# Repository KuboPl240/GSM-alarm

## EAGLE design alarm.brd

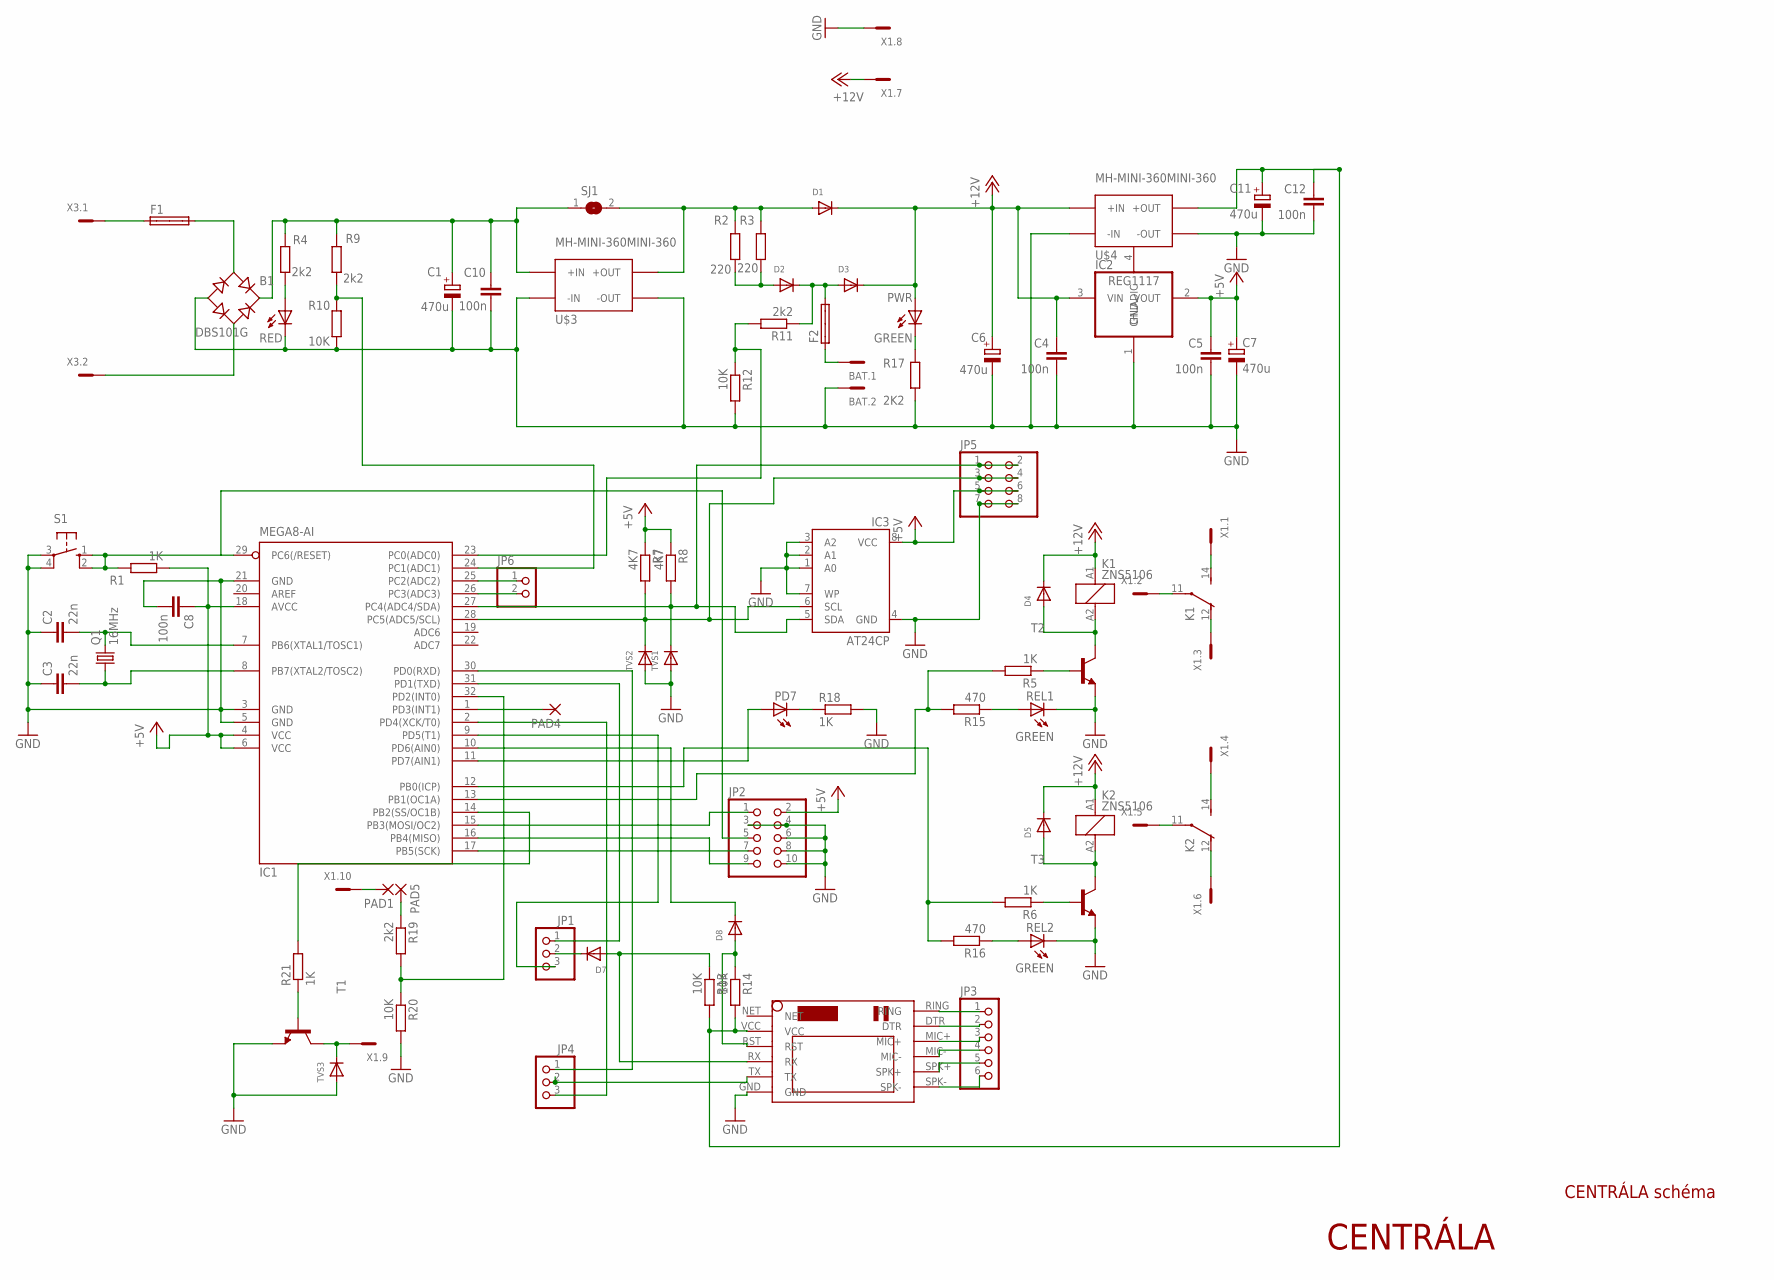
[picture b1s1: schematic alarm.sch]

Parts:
B1: DBS101G; DBS
BAT: MCV2
C1, C6, C7, C11: 470u; 153CLV-0810
C2, C3: 22n; C0805
C4, C5, C8, C10, C12: 100n; C0805
D1, D2, D3, D4, D5, D7, D8: DIODE_SOD-123FL; SOD-123FL
F1, F2: SHK20L
IC1: MEGA8-AI; TQFP32-08
IC2: REG1117; SOT223
IC3: AT24CP; DIL08
JP1, JP4: PINHD-1X3; 1X03
JP2: PINHD-2X5; 2X05
JP3: PINHD-1X6; 1X06
JP5: PINHD-2X4; 2X04
JP6: PINHD-1X2; 1X02
K1, K2: ZNS5106; ZN5
PAD1, PAD4, PAD5: 2,54/0,8
PD7: LEDCHIPLED_0805; CHIPLED_0805
PWR: GREEN; CHIPLED_0805
Q1: 16MHz; HC49UP
R1, R5, R6, R18, R21: 1K; R0805
R2, R3: 220; R1210
R4, R9, R11, R19: 2k2; R0805
R7, R8: 4K7; R0805
R10, R12, R13, R14, R20: 10K; R0805
R15, R16: 470; R0805
R17: 2K2; R0805
REL1, REL2: GREEN; CHIPLED_0805
S1: 10-XX; B3F-10XX
SJ1: SJW
SUPPLY: RED; CHIPLED_0805
T1, T2, T3: BC808-NPN-SOT23-BEC; SOT23-BEC
TVS1, TVS2, TVS3: DIODE_SOD-123FL; SOD-123FL
U$1: SIM800LMODULE
U$3, U$4: MH-MINI-360MINI-360; MH-MINI-360
X1: MCV10
X3: MCV2

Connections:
+4.4V: C11.+, C12.2, R13.2, R14.2, U$1.VCC, U$4.P$3 (+OUT)
+5V: C5.2, C7.+, C8.1, IC1.4 (VCC), IC1.6 (VCC), IC1.18 (AVCC), IC2.2 (VOUT), IC3.8 (VCC), JP2.2, JP5.5, JP5.6, R1.1, R7.1, R8.1
+12V: C4.2, C6.+, D1.C, D3.C, D4.C, D5.C, IC2.3 (VIN), K1.A1 (1), K2.A1 (1), PWR.A, U$4.P$2 (+IN), X1.7
CHLADIC: IC2.4 (CHLADIC)
GND: B1.-, BAT.2, C1.-, C2.1, C3.1, C4.1, C5.1, C6.-, C7.-, C8.2, C10.1, C11.-, C12.1, IC1.3 (GND), IC1.5 (GND), IC1.21 (GND), IC2.1 (GND), IC3.1 (A0), IC3.2 (A1), IC3.3 (A2), IC3.4 (GND), IC3.7 (WP), JP2.3, JP2.4, JP2.6, JP2.8, JP2.10, JP5.7, JP5.8, R10.2, R12.2, R17.2, R18.2, R20.2, REL1.C, REL2.C, S1.3, S1.4 (P1), SUPPLY.C, T1.E, T2.E, T3.E, TVS1.A, TVS2.A, TVS3.A, U$1.GND, U$3.P$1 (-IN), U$3.P$4 (-OUT), U$4.P$1 (-IN), U$4.P$4 (-OUT), X1.8
unnamed: B1.AC1, F1.2A
unnamed: B1.AC2, X3.2
unnamed: B1.+, C1.+, C10.2, R4.1, R9.1, SJ1.1, U$3.P$2 (+IN)
unnamed: JP3.6, U$1.SPK-
unnamed: D1.A, R2.2, R3.2, SJ1.2, U$3.P$3 (+OUT)
unnamed: D2.A, R2.1, R3.1
unnamed: D2.C, D3.A, F2.2A, R11.1
unnamed: BAT.1, F2.1A
unnamed: C3.2, IC1.8 (PB7(XTAL2/TOSC2)), Q1.1
unnamed: F1.1A, X3.1
unnamed: IC1.15 (PB3(MOSI/OC2)), JP2.1
unnamed: C2.2, IC1.7 (PB6(XTAL1/TOSC1)), Q1.2
unnamed: IC1.17 (PB5(SCK)), JP2.7
unnamed: R4.2, SUPPLY.A
unnamed: IC1.29 (PC6(/RESET)), JP2.5, R1.2, S1.1 (S), S1.2 (S1)
unnamed: IC1.16 (PB4(MISO)), JP2.9
unnamed: IC1.28 (PC5(ADC5/SCL)), IC3.6 (SCL), JP5.3, JP5.4, R7.2, TVS2.C
unnamed: PAD1.1, X1.10
unnamed: IC1.24 (PC1(ADC1)), R9.2, R10.1
unnamed: D5.A, K2.A2 (2), T3.C
unnamed: D4.A, K1.A2 (2), T2.C
unnamed: R5.1, T2.B
unnamed: R6.1, T3.B
unnamed: IC1.13 (PB1(OC1A)), R5.2, R15.2
unnamed: K1.14 (S), X1.1
unnamed: K1.11, X1.2
unnamed: K1.12 (O), X1.3
unnamed: K2.14 (S), X1.4
unnamed: K2.11, X1.5
unnamed: K2.12 (O), X1.6
unnamed: IC1.23 (PC0(ADC0)), R11.2, R12.1
unnamed: JP3.5, U$1.SPK+
unnamed: JP3.4, U$1.MIC-
unnamed: JP3.3, U$1.MIC+
unnamed: JP3.2, U$1.DTR
unnamed: JP3.1, U$1.RING
unnamed: JP4.2, U$1.TX
unnamed: D7.A, R13.1, U$1.RX
unnamed: IC1.31 (PD1(TXD)), JP1.1
unnamed: IC1.30 (PD0(RXD)), JP4.1
unnamed: IC1.2 (PD4(XCK/T0)), JP4.3
unnamed: D7.C, JP1.2
unnamed: IC1.9 (PD5(T1)), JP1.3
unnamed: D8.A, R14.1, U$1.RST
unnamed: R16.1, REL2.A
unnamed: D8.C, IC1.10 (PD6(AIN0))
unnamed: R15.1, REL1.A
unnamed: PWR.C, R17.1
unnamed: PD7.C, R18.1
unnamed: IC1.11 (PD7(AIN1)), PD7.A
unnamed: IC1.27 (PC4(ADC4/SDA)), IC3.5 (SDA), JP5.1, JP5.2, R8.2, TVS1.C
unnamed: IC1.32 (PD2(INT0)), R19.2, R20.1
unnamed: IC1.14 (PB2(SS/OC1B)), R21.2
unnamed: IC1.25 (PC2(ADC2)), JP6.1
unnamed: IC1.26 (PC3(ADC3)), JP6.2
unnamed: IC1.1 (PD3(INT1)), PAD4.1
unnamed: R21.1, T1.B
unnamed: T1.C, TVS3.C, X1.9
unnamed: PAD5.1, R19.1
unnamed: IC1.12 (PB0(ICP)), R6.2, R16.2

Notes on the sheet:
CENTRÁLA
CENTRÁLA schéma

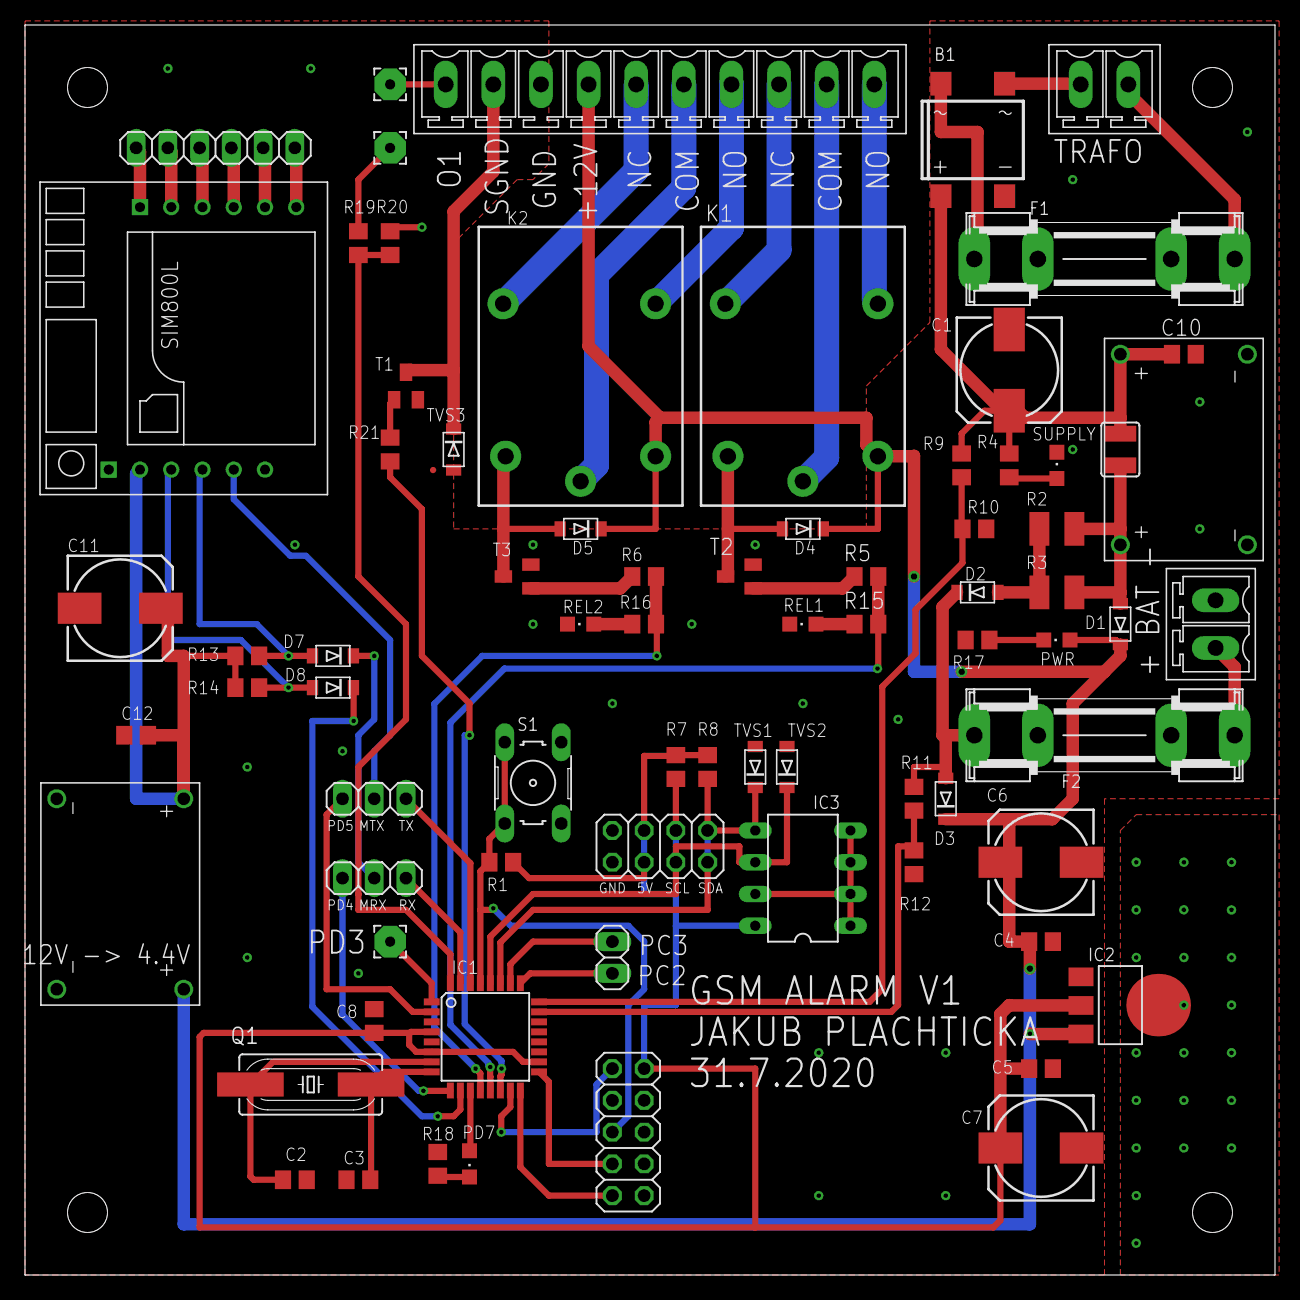
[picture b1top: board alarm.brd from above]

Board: 2 copper layers, 100.0 x 100.0 mm, 76 parts (0 on the bottom side), 64 nets.

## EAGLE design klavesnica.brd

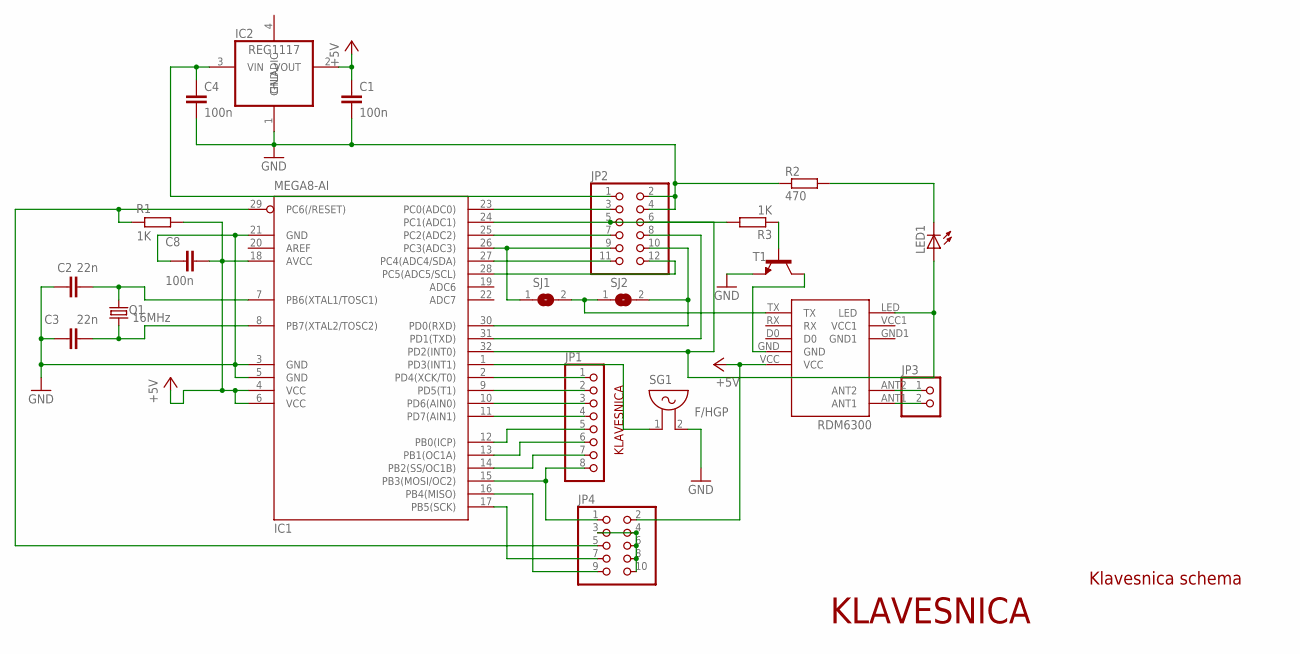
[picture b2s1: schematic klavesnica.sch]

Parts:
C1, C4, C8: 100n; C0805
C2, C3: 22n; C0805
IC1: MEGA8-AI; TQFP32-08
IC2: REG1117; SOT223
JP1: PINHD-1X8; 1X08
JP2: PINHD-2X6; 2X06
JP3: PINHD-1X2; 1X02
JP4: PINHD-2X5; 2X05
LED1: LED3MM
Q1: 16MHz; HC49UP
R1, R3: 1K; R0805
R2: 470; R0805
RDM1: RDM6300
SG1: F/HGP
SJ1, SJ2: SJ
T1: BC808-NPN-SOT23-BEC; SOT23-BEC

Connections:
+5V: C1.1, C8.1, IC1.4 (VCC), IC1.6 (VCC), IC1.18 (AVCC), IC2.2 (VOUT), JP4.2, R1.1, RDM1.VCC
CHLADIC: IC2.4 (CHLADIC)
GND: C1.2, C2.1, C3.1, C4.2, C8.2, IC1.3 (GND), IC1.5 (GND), IC1.21 (GND), IC2.1 (GND), JP2.2, JP2.4, R2.1, SG1.2, T1.E
unnamed: IC1.29 (PC6(/RESET)), JP4.5, R1.2
unnamed: IC1.2 (PD4(XCK/T0)), JP1.1
unnamed: IC1.9 (PD5(T1)), JP1.2
unnamed: IC1.10 (PD6(AIN0)), JP1.3
unnamed: IC1.11 (PD7(AIN1)), JP1.4
unnamed: IC1.12 (PB0(ICP)), JP1.5
unnamed: IC1.13 (PB1(OC1A)), JP1.6
unnamed: IC1.14 (PB2(SS/OC1B)), JP1.7
unnamed: C3.2, IC1.8 (PB7(XTAL2/TOSC2)), Q1.1
unnamed: C4.1, IC2.3 (VIN), JP2.1
unnamed: LED1.K (C), R2.2
unnamed: C2.2, IC1.7 (PB6(XTAL1/TOSC1)), Q1.2
unnamed: IC1.23 (PC0(ADC0)), JP2.3
unnamed: IC1.24 (PC1(ADC1)), JP2.5, R3.2
unnamed: IC1.25 (PC2(ADC2)), JP2.7
unnamed: IC1.26 (PC3(ADC3)), JP2.9, SJ1.1
unnamed: IC1.27 (PC4(ADC4/SDA)), JP2.11
unnamed: IC1.28 (PC5(ADC5/SCL)), JP2.12
unnamed: IC1.30 (PD0(RXD)), JP2.10, SJ2.2
unnamed: IC1.31 (PD1(TXD)), JP2.8
unnamed: IC1.1 (PD3(INT1)), SG1.1
unnamed: JP3.1, RDM1.ANT2
unnamed: JP3.2, RDM1.ANT1
unnamed: JP4.3, JP4.4, JP4.6, JP4.8, JP4.10
unnamed: IC1.32 (PD2(INT0)), JP2.6, LED1.A, RDM1.LED
unnamed: IC1.16 (PB4(MISO)), JP4.9
unnamed: IC1.17 (PB5(SCK)), JP4.7
unnamed: RDM1.GND, T1.C
unnamed: IC1.15 (PB3(MOSI/OC2)), JP1.8, JP4.1
unnamed: R3.1, T1.B
unnamed: RDM1.TX, SJ1.2, SJ2.1

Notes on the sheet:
KLAVESNICA
Klavesnica schema

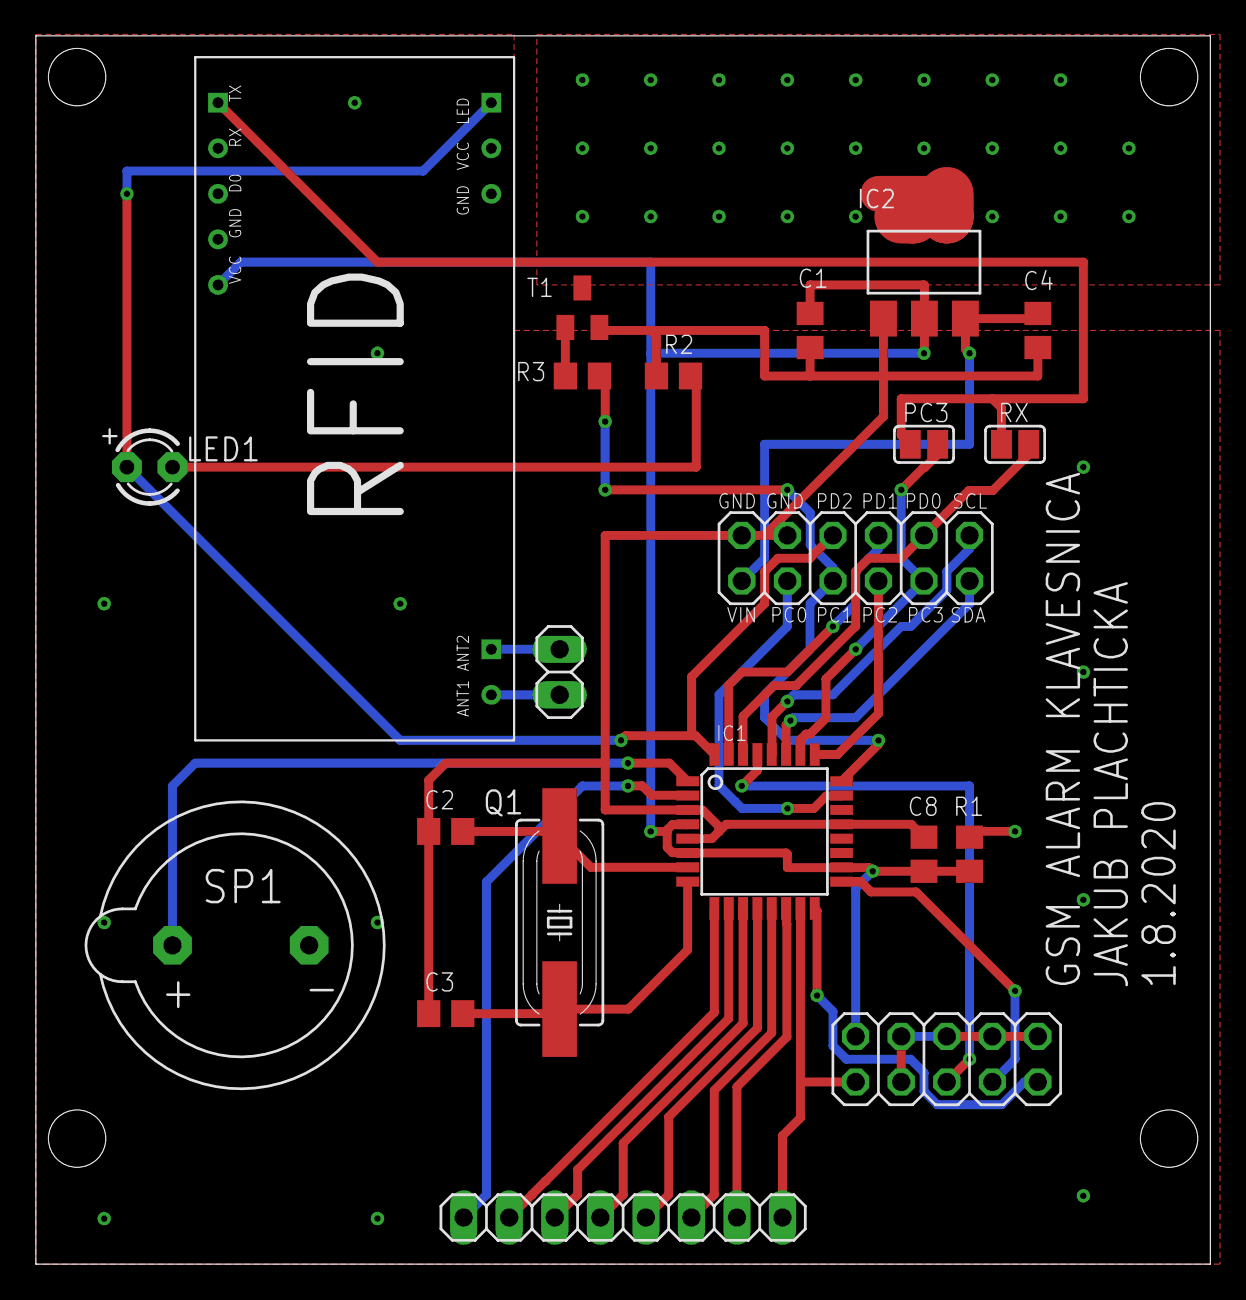
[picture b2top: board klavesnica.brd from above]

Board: 2 copper layers, 65.5 x 68.5 mm, 21 parts (0 on the bottom side), 33 nets.
